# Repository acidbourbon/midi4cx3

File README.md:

This repository contains the firmware and PCB design source files of a microcontroller
project that adds a MIDI output to a vintage Korg CX-3 organ.

for details visit
https://acidbourbon.wordpress.com/2013/04/02/midi-out-for-vintage-korg-cx-3/

2011 by Michael Wiebusch
mwiebusch.de

Note: 2026
Updated the pcb. Cleaned up KiCAD project, made it 2 layer board, ready to order
from JLCPCB.

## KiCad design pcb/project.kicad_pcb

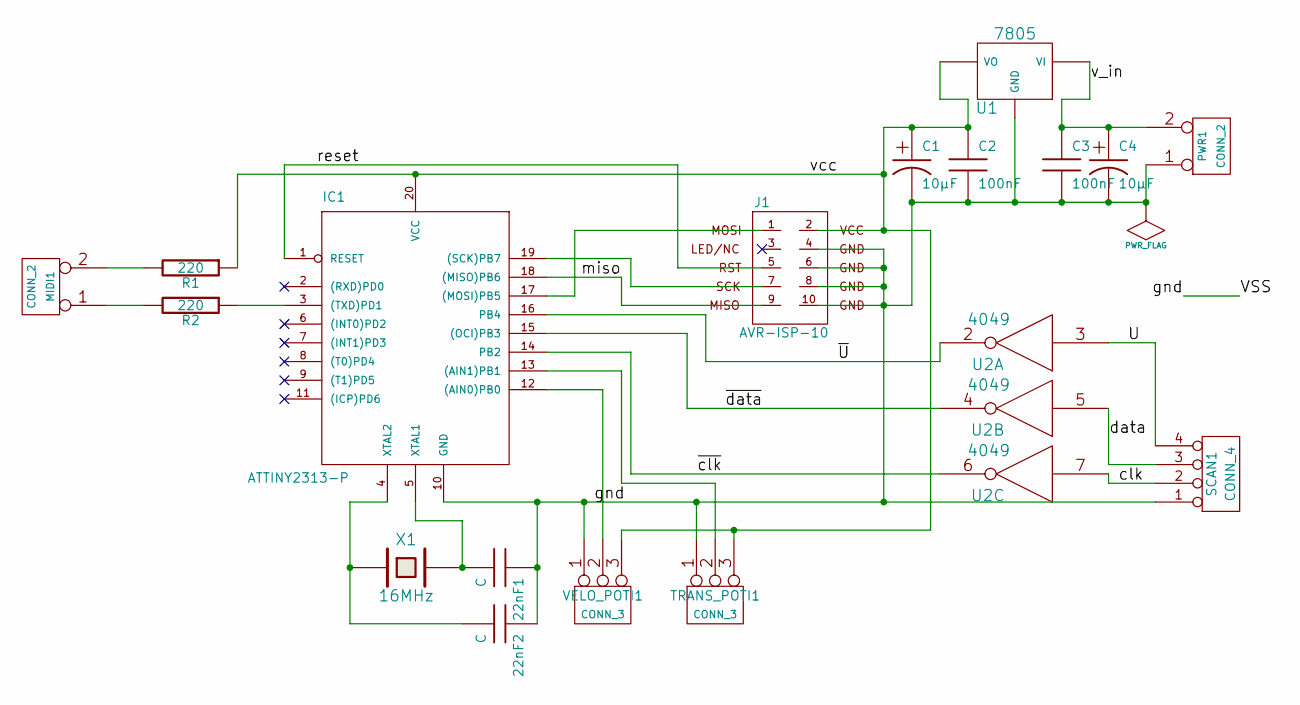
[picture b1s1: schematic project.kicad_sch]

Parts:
22nF1, 22nF2: C
C1, C4: 10µF
C2, C3: 100nF
IC1: ATTINY2313-P; DIL20
J1: AVR-ISP-10
MIDI1: CONN_2
PWR1: CONN_2
R1, R2: 220
SCAN1: CONN_4
TRANS_POTI1: CONN_3
U1: 7805
U2: 4049
VELO_POTI1: CONN_3
X1: 16MHz

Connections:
/U: SCAN1.4, U2.3
/clk: SCAN1.2, U2.7
/data: SCAN1.3, U2.5
/gnd: 22nF1.1, 22nF2.1, C1.2, C2.2, C3.2, C4.2, IC1.10 (GND), J1.4, J1.6, J1.8, J1.10, PWR1.1, SCAN1.1, TRANS_POTI1.1, U1.GND, U2.8 (VSS), VELO_POTI1.1
/miso: IC1.18 ((MISO)PB6), J1.9
/reset: IC1.1 (RESET), J1.5
/v_in: C3.1, C4.1, PWR1.2 (PM), U1.VI
/vcc: C1.1, C2.1, IC1.20 (VCC), J1.2, R1.1, TRANS_POTI1.3, U1.VO, U2.1 (VCC), VELO_POTI1.3
/~U: IC1.16 (PB4), U2.2
/~clk: IC1.14 (PB2), U2.6
/~data: IC1.15 ((OCI)PB3), U2.4
unnamed: IC1.13 ((AIN1)PB1), TRANS_POTI1.2 (PM)
unnamed: IC1.12 ((AIN0)PB0), VELO_POTI1.2 (PM)
unnamed: MIDI1.2 (PM), R1.2
unnamed: MIDI1.1, R2.2
unnamed: IC1.3 ((TXD)PD1), R2.1
unnamed: 22nF1.2, IC1.5 (XTAL1), X1.2
unnamed: IC1.17 ((MOSI)PB5), J1.1
unnamed: 22nF2.2, IC1.4 (XTAL2), X1.1
unnamed: IC1.19 ((SCK)PB7), J1.7

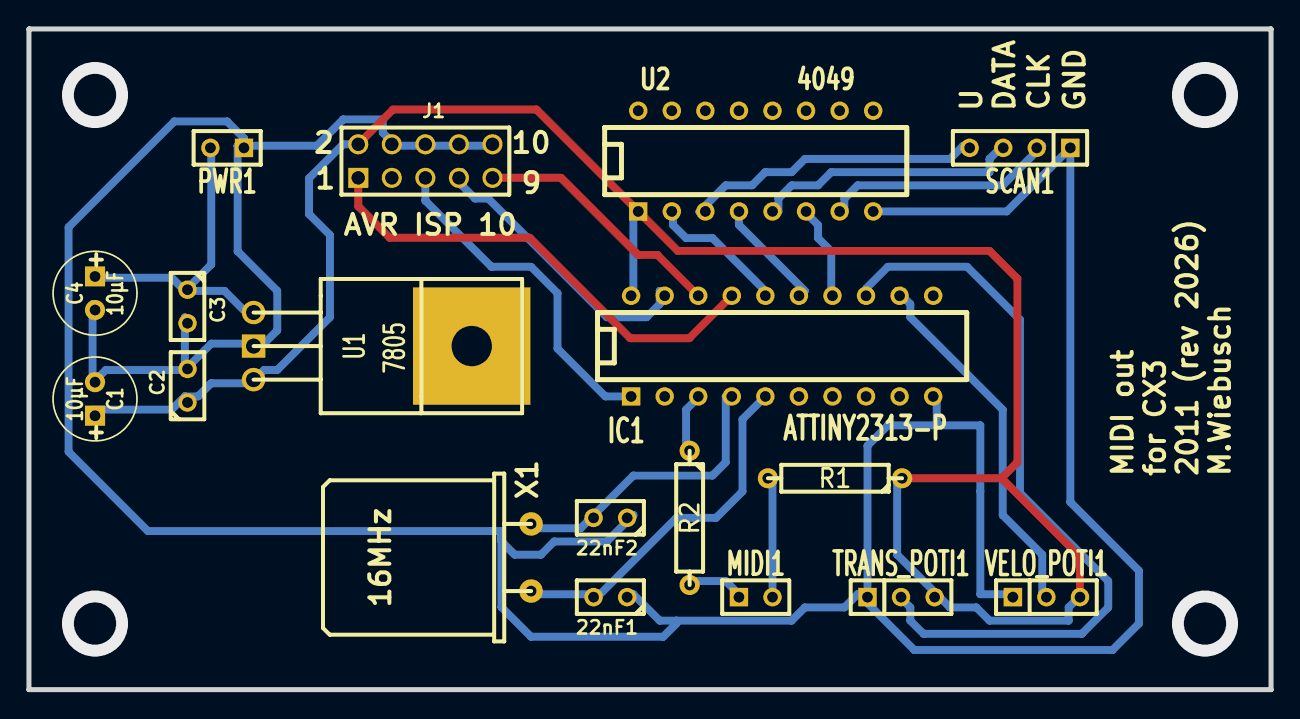
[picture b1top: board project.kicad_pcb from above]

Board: 2 copper layers, 94.0 x 50.0 mm, 18 parts (0 on the bottom side), 20 nets.

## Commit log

2014-09-28 this is in my organ
2016-03-09 added pcb files
2016-03-09 added README message for github
2026-02-23 removed stale backup files
2026-02-23 cleaned up KiCAD Project, made 2 layer board
